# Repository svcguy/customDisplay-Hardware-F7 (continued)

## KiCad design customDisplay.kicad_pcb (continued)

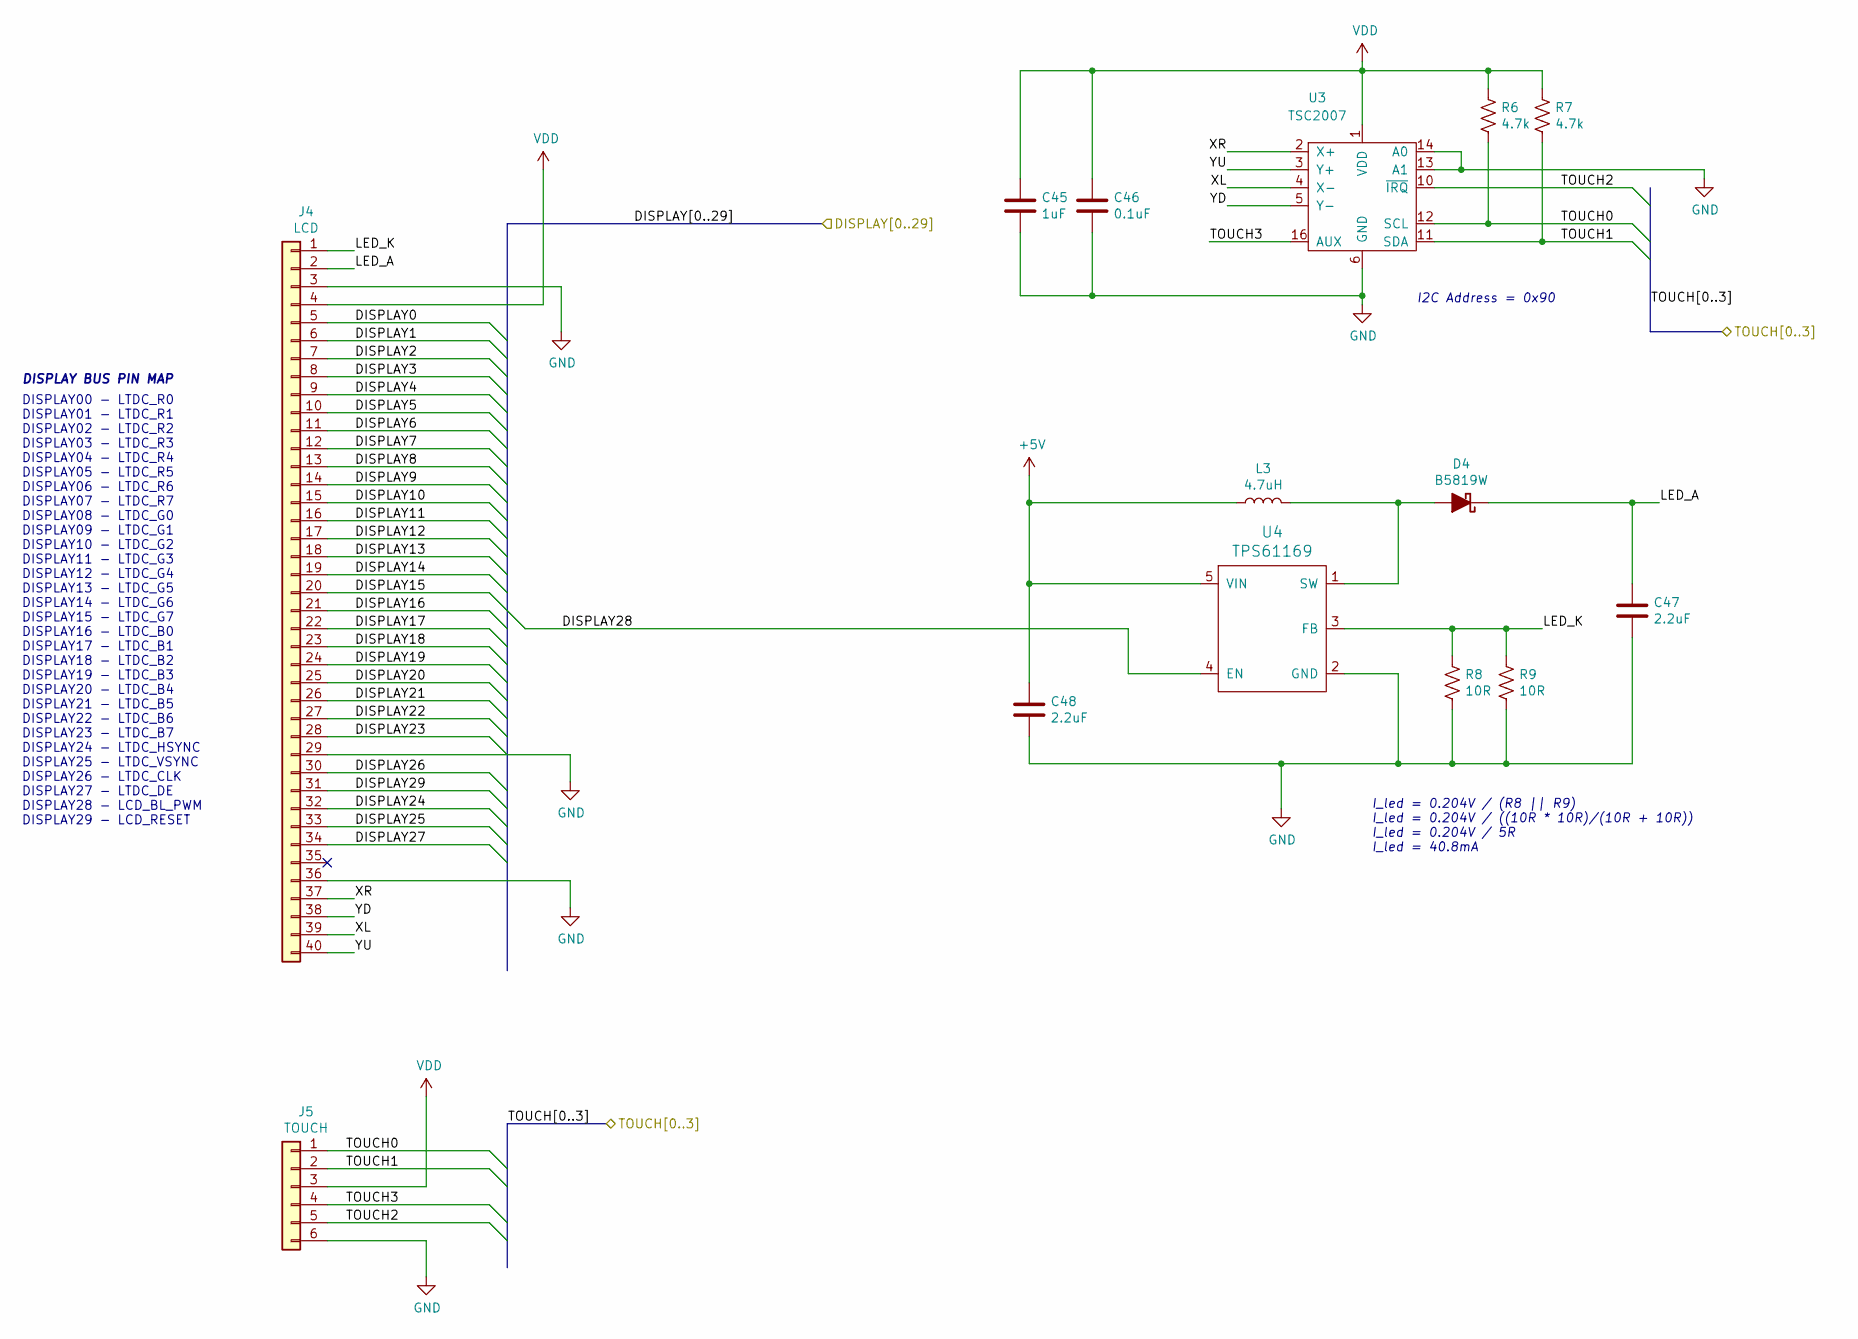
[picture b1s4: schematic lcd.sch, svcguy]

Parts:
C45: 1uF; C_0402_1005Metric; LCSC C52923
C46: 0.1uF; C_0402_1005Metric; LCSC C1525
C47, C48: 2.2uF; C_0603_1608Metric; LCSC C23630
D4: B5819W; D_SOD-123; LCSC C8598
J4: LCD; FH12A-40S-0.5SH_REVERSE_PIN_NUMBERING; LCSC C262686
J5: TOUCH; Hirose_FH12-6S-0.5SH_1x06-1MP_P0.50mm_Horizontal; LCSC C262287
L3: 4.7uH; MWSA0402; LCSC C408337
R6, R7: 4.7k; R_0402_1005Metric; LCSC C25900
R8, R9: 10R; R_1206_3216Metric; LCSC C17903
U3: TSC2007; HTSSOP-16-1EP_4.4x5mm_P0.65mm_EP3x3mm; LCSC C38398
U4: TPS61169; SC70; LCSC C71045

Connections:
+5V: C48.1, L3.1, U4.5 (VIN); also elsewhere on the board
/LCD/DISPLAY0: J4.5; also elsewhere on the board
/LCD/DISPLAY1: J4.6; also elsewhere on the board
/LCD/DISPLAY2: J4.7; also elsewhere on the board
/LCD/DISPLAY3: J4.8; also elsewhere on the board
/LCD/DISPLAY4: J4.9; also elsewhere on the board
/LCD/DISPLAY5: J4.10; also elsewhere on the board
/LCD/DISPLAY6: J4.11; also elsewhere on the board
/LCD/DISPLAY7: J4.12; also elsewhere on the board
/LCD/DISPLAY8: J4.13; also elsewhere on the board
/LCD/DISPLAY9: J4.14; also elsewhere on the board
/LCD/DISPLAY10: J4.15; also elsewhere on the board
/LCD/DISPLAY11: J4.16; also elsewhere on the board
/LCD/DISPLAY12: J4.17; also elsewhere on the board
/LCD/DISPLAY13: J4.18; also elsewhere on the board
/LCD/DISPLAY14: J4.19; also elsewhere on the board
/LCD/DISPLAY15: J4.20; also elsewhere on the board
/LCD/DISPLAY16: J4.21; also elsewhere on the board
/LCD/DISPLAY17: J4.22; also elsewhere on the board
/LCD/DISPLAY18: J4.23; also elsewhere on the board
/LCD/DISPLAY19: J4.24; also elsewhere on the board
/LCD/DISPLAY20: J4.25; also elsewhere on the board
/LCD/DISPLAY21: J4.26; also elsewhere on the board
/LCD/DISPLAY22: J4.27; also elsewhere on the board
/LCD/DISPLAY23: J4.28; also elsewhere on the board
/LCD/DISPLAY24: J4.32; also elsewhere on the board
/LCD/DISPLAY25: J4.33; also elsewhere on the board
/LCD/DISPLAY26: J4.30; also elsewhere on the board
/LCD/DISPLAY27: J4.34; also elsewhere on the board
/LCD/DISPLAY28: U4.4 (EN); also elsewhere on the board
/LCD/DISPLAY29: J4.31; also elsewhere on the board
/LCD/LED_A: C47.1, D4.1 (K), J4.2
/LCD/LED_K: J4.1, R8.1, R9.1, U4.3 (FB)
/LCD/TOUCH2: J5.5, U3.10 (~IRQ); also elsewhere on the board
/LCD/TOUCH3: J5.4, U3.16 (AUX); also elsewhere on the board
/LCD/XL: J4.39, U3.4 (X-)
/LCD/XR: J4.37, U3.2 (X+)
/LCD/YD: J4.38, U3.5 (Y-)
/LCD/YU: J4.40, U3.3 (Y+)
/TOUCH0: J5.1, R6.2, U3.12 (SCL); also elsewhere on the board
/TOUCH1: J5.2, R7.2, U3.11 (SDA); also elsewhere on the board
GND: C45.2, C46.2, C47.2, C48.2, J4.3, J4.29, J4.36, J5.6, R8.2, R9.2, U3.6 (GND), U3.13 (A1), U3.14 (A0), U3.17, U4.2 (GND); also elsewhere on the board
unnamed: D4.2 (A), L3.2, U4.1 (SW)
VDD: C45.1, C46.1, J4.4, J5.3, R6.1, R7.1, U3.1 (VDD); also elsewhere on the board

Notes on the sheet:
DISPLAY BUS PIN MAP
DISPLAY00 - LTDC_R0 DISPLAY01 - LTDC_R1 DISPLAY02 - LTDC_R2 DISPLAY03 - LTDC_R3 DISPLAY04 - LTDC_R4 DISPLAY05 - LTDC_R5 DISPLAY06 - LTDC_R6 DISPLAY07 - LTDC_R7 DISPLAY08 - LTDC_G0 DISPLAY09 - LTDC_G1 DISPLAY10 - LTDC_G2 DISPLAY11 - LTDC_G3 DISPLAY12 - LTDC_G4 DISPLAY13 - LTDC_G5 DISPLAY14 - LTDC_G6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
I_led = 0.204V / (R8 || R9) I_led = 0.204V / ((10R * 10R)/(10R + 10R)) I_led = 0.204V / 5R I_led = 40.8mA
I2C Address = 0x90

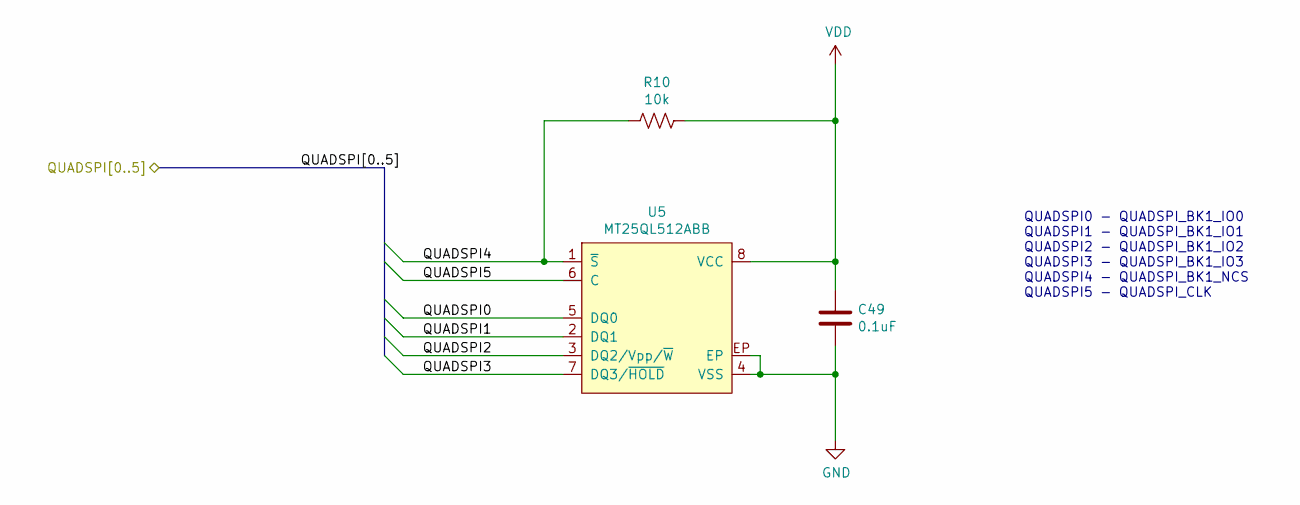
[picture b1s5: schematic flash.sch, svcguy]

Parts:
C49: 0.1uF; C_0402_1005Metric; LCSC C1525
R10: 10k; R_0402_1005Metric; LCSC C25744
U5: MT25QL512ABB; W-PDFN-8; LCSC C88868

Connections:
/Flash/QUADSPI0: U5.5 (DQ0); also elsewhere on the board
/Flash/QUADSPI1: U5.2 (DQ1); also elsewhere on the board
/Flash/QUADSPI2: U5.3 (DQ2/Vpp/~W); also elsewhere on the board
/Flash/QUADSPI3: U5.7 (DQ3/~HOLD); also elsewhere on the board
/Flash/QUADSPI4: R10.2, U5.1 (~S); also elsewhere on the board
/Flash/QUADSPI5: U5.6 (C); also elsewhere on the board
GND: C49.2, U5.4 (VSS), U5.12, U5.EP; also elsewhere on the board
VDD: C49.1, R10.1, U5.8 (VCC); also elsewhere on the board

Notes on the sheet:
QUADSPI0 - QUADSPI_BK1_IO0 QUADSPI1 - QUADSPI_BK1_IO1 QUADSPI2 - QUADSPI_BK1_IO2 QUADSPI3 - QUADSPI_BK1_IO3 QUADSPI4 - QUADSPI_BK1_NCS QUADSPI5 - QUADSPI_CLK

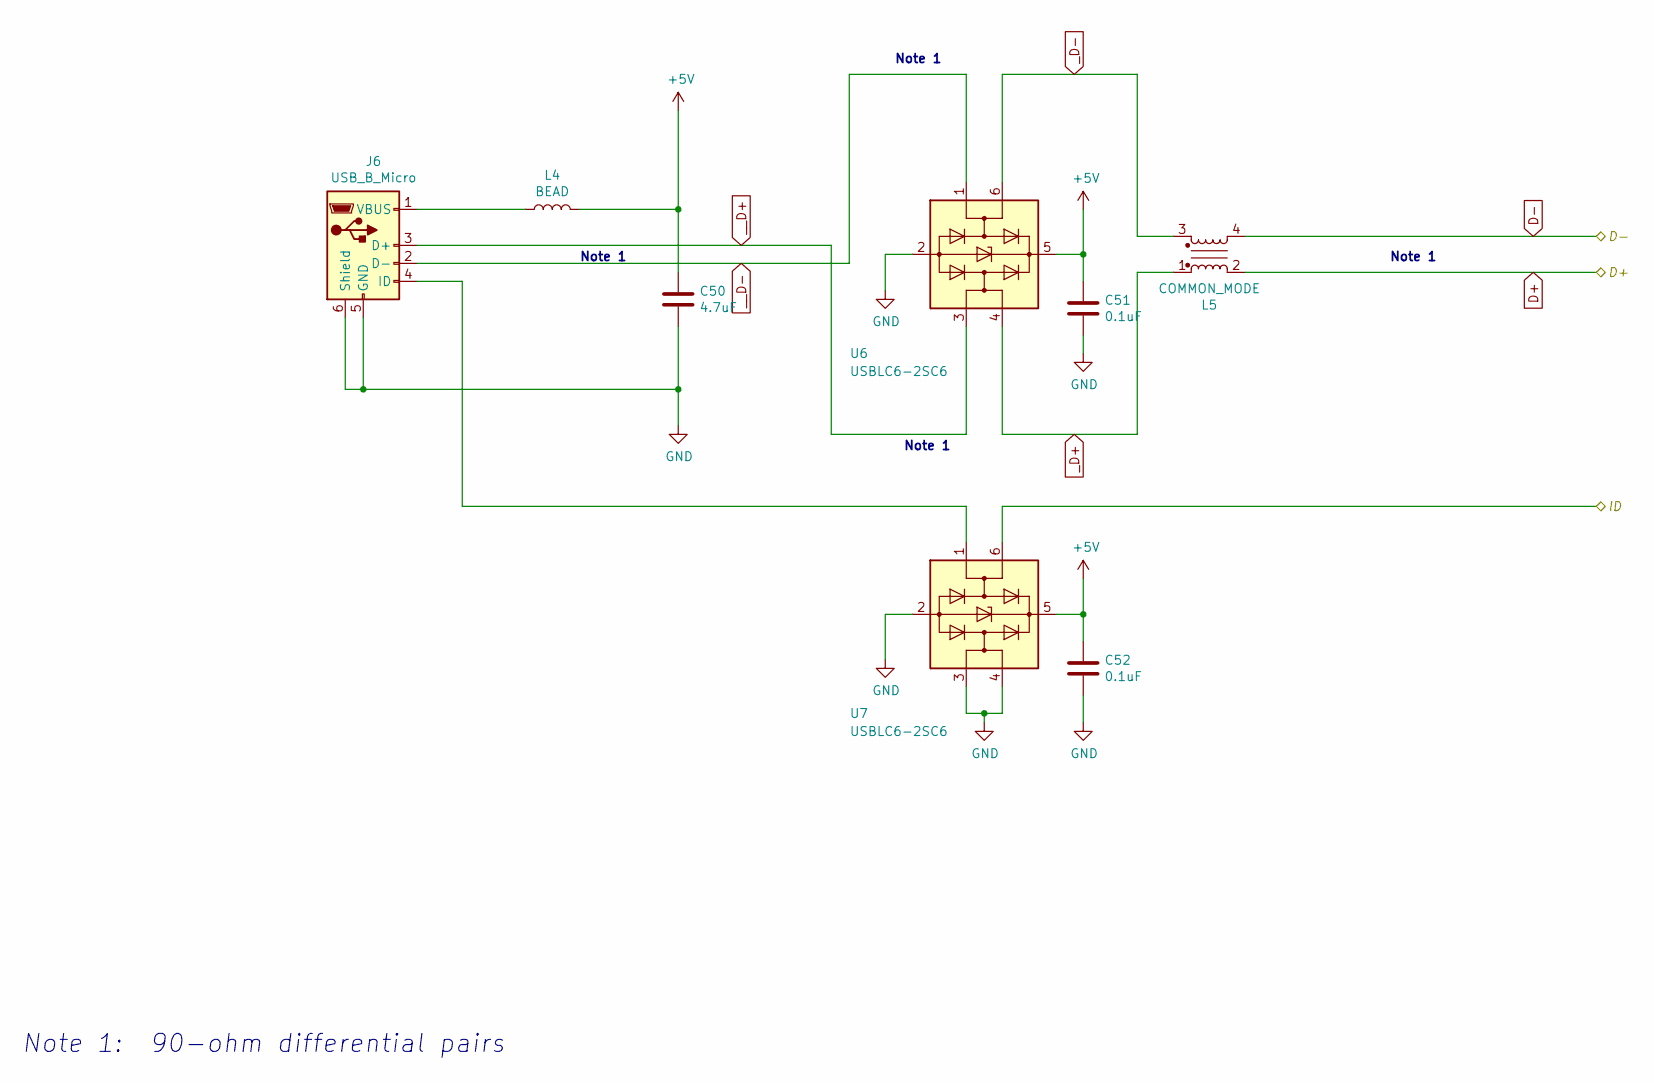
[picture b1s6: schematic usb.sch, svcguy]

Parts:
C50: 4.7uF; C_0805_2012Metric; LCSC C1779
C51, C52: 0.1uF; C_0402_1005Metric; LCSC C1525
J6: USB_B_Micro; USB_Micro-B_Amphenol_10103594-0001LF_Horizontal; LCSC C428495
L4: BEAD; L_0805_2012Metric; LCSC C1015
L5: COMMON_MODE; COMMON_MODE_FILTER_0805; LCSC C54888
U6, U7: USBLC6-2SC6; SOT-23-6; LCSC C7519

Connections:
+5V: C50.1, C51.1, C52.1, L4.2, U6.5 (VBUS), U7.5 (VBUS); also elsewhere on the board
/USB/ID: U7.6 (I/O1); also elsewhere on the board
D+: L5.2; also elsewhere on the board
D-: L5.4; also elsewhere on the board
GND: C50.2, C51.2, C52.2, J6.5 (GND), J6.6 (Shield), U6.2 (GND), U7.2 (GND), U7.3 (I/O2), U7.4 (I/O2); also elsewhere on the board
unnamed: J6.1 (VBUS), L4.1
unnamed: J6.4 (ID), U7.1 (I/O1)
_D+: L5.1, U6.4 (I/O2)
_D-: L5.3, U6.6 (I/O1)
__D+: J6.3 (D+), U6.3 (I/O2)
__D-: J6.2 (D-), U6.1 (I/O1)

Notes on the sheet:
Note 1
Note 1: 90-ohm differential pairs

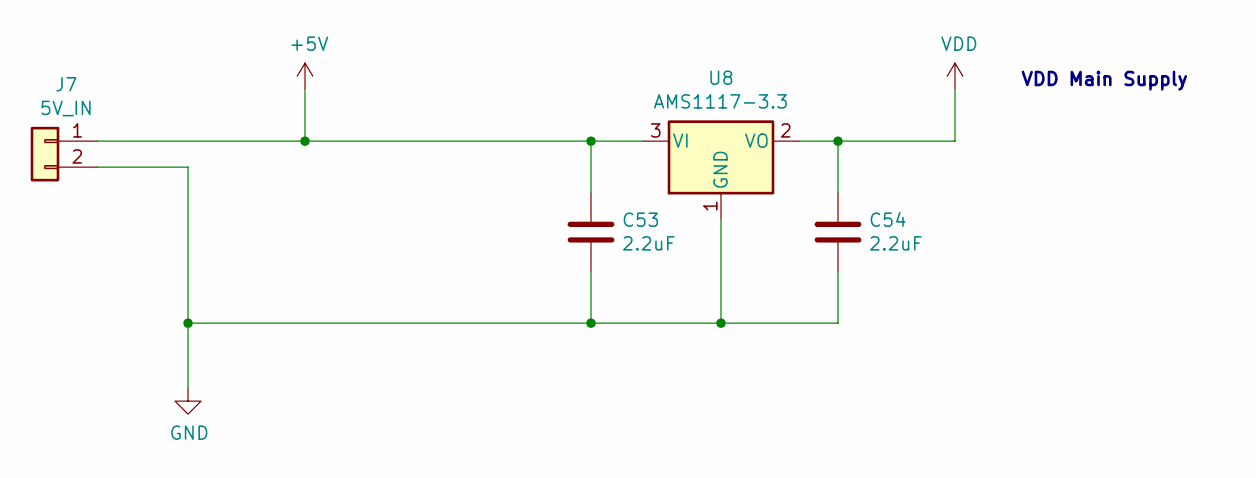
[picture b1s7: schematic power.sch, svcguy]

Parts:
C53, C54: 2.2uF; C_0603_1608Metric; LCSC C23630
J7: 5V_IN; PinHeader_1x02_P2.54mm_Vertical; LCSC DNP
U8: AMS1117-3.3; SOT-223-3_TabPin2; LCSC C6186

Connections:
+5V: C53.1, J7.1, U8.3 (VI); also elsewhere on the board
GND: C53.2, C54.2, J7.2, U8.1 (GND); also elsewhere on the board
VDD: C54.1, U8.2 (VO); also elsewhere on the board

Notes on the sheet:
VDD Main Supply

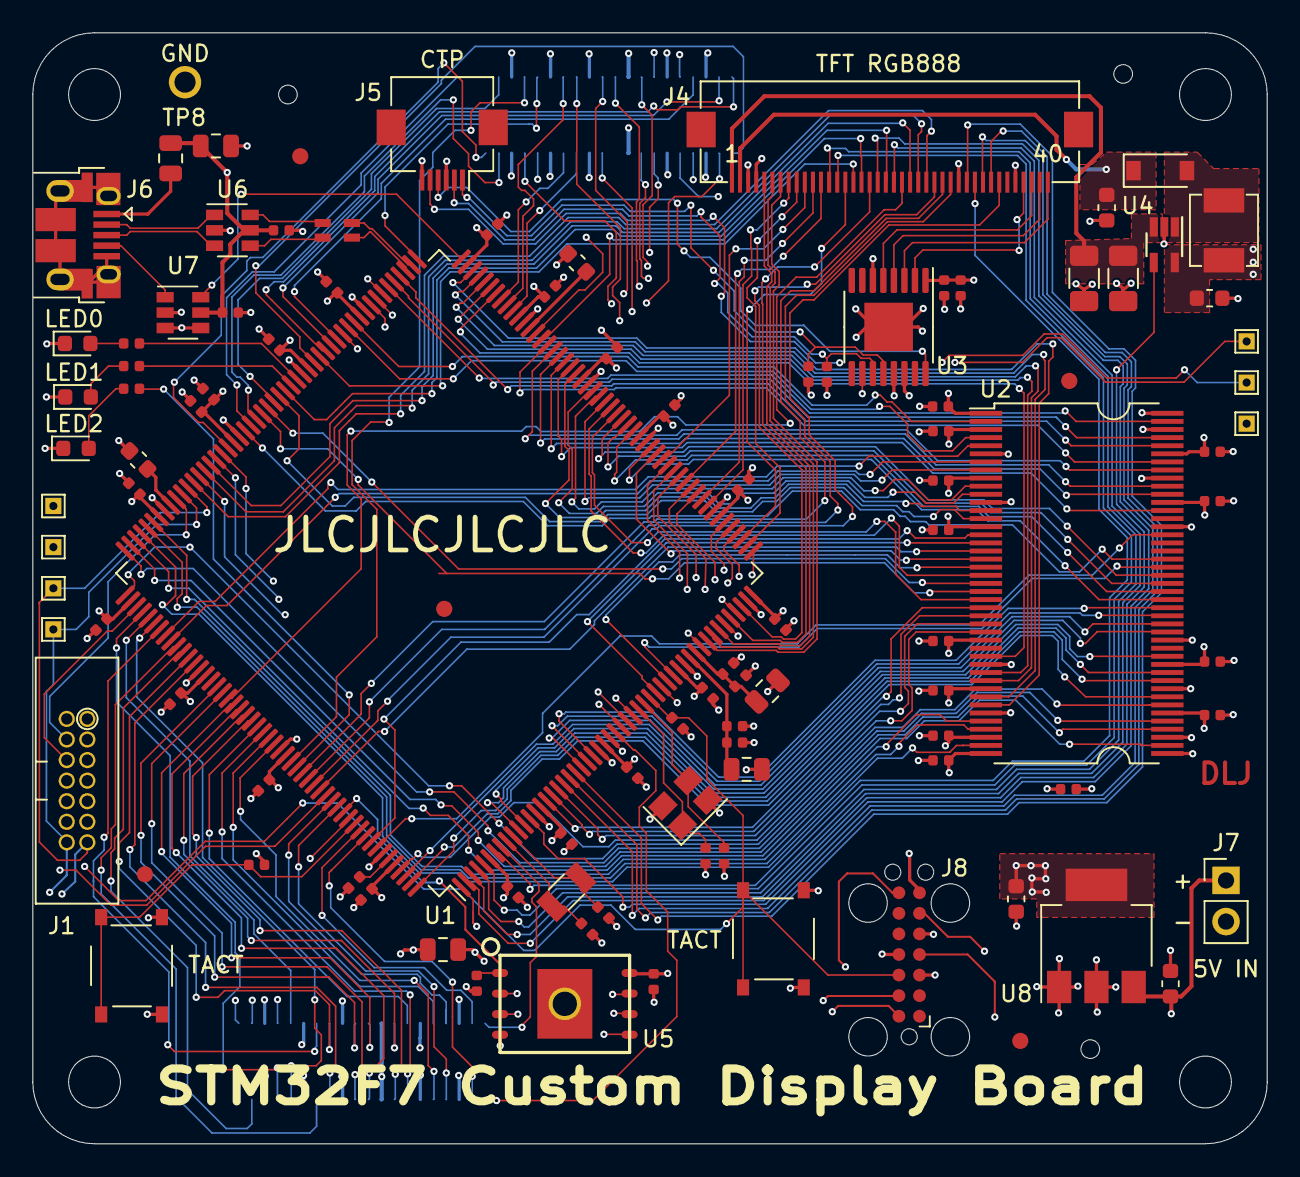
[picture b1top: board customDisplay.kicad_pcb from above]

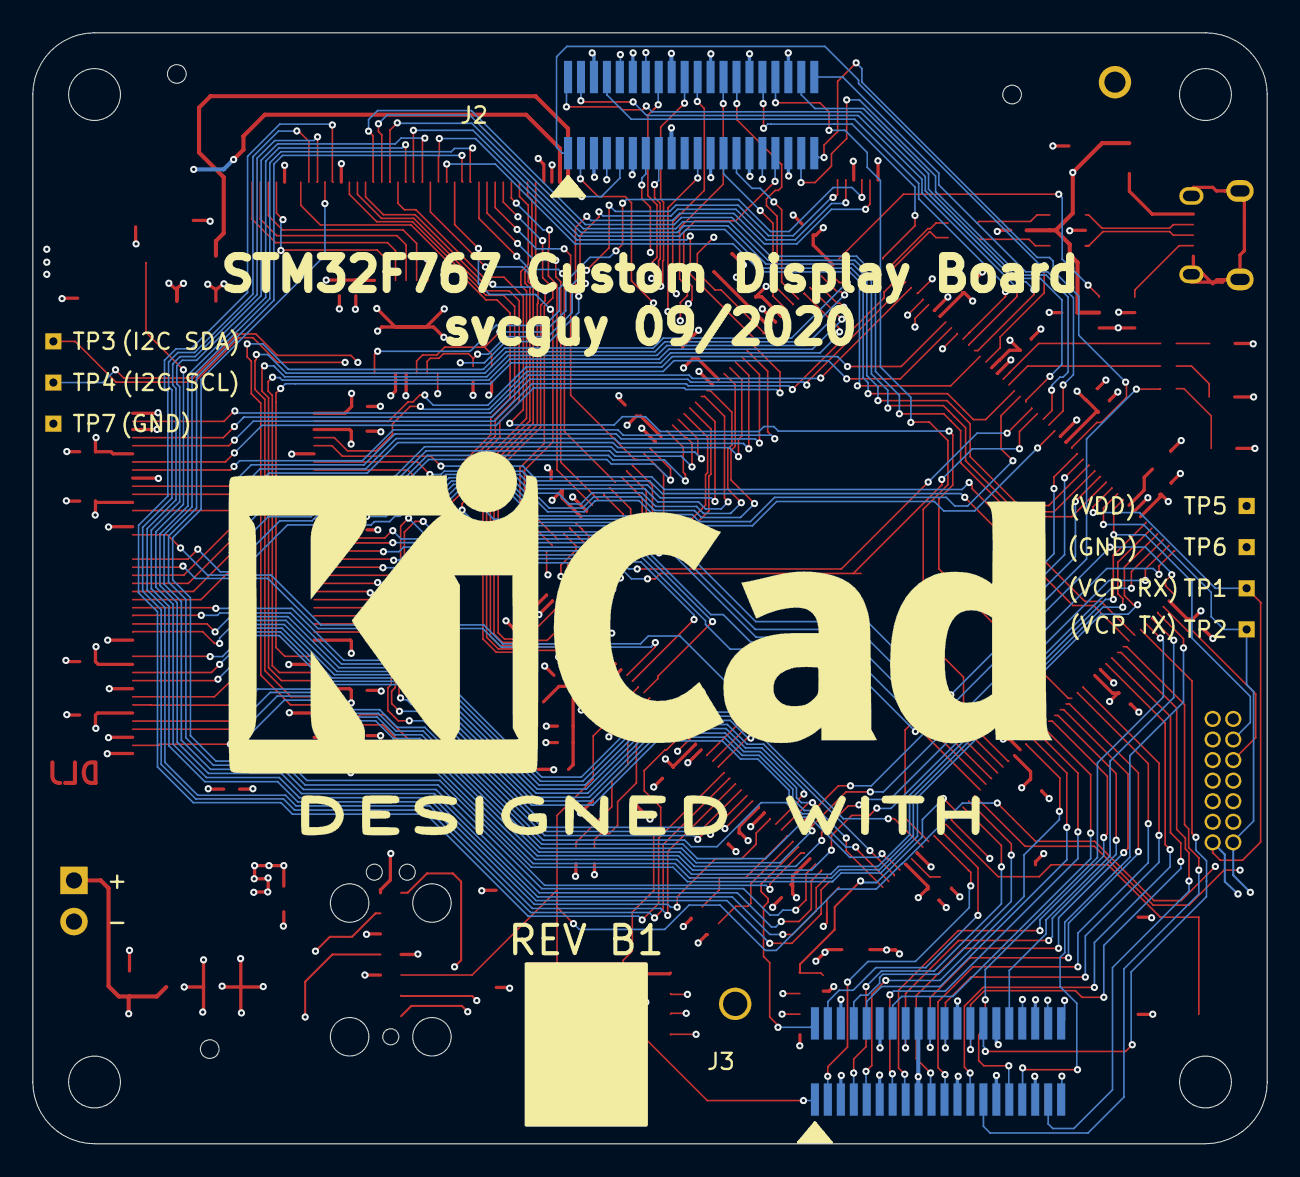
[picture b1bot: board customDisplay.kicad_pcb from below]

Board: 4 copper layers, 76.2 x 68.6 mm, 113 parts (2 on the bottom side), 193 nets.

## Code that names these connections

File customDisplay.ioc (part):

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Mcu.Name=STM32F767B(G-I)Tx
Mcu.Package=LQFP208
Mcu.UserName=STM32F767BGTx
PA1.Mode=RGB888
PA1.Signal=LTDC_R2
PA10.Mode=RGB888
PA10.Signal=LTDC_B4
PA11.GPIOParameters=GPIO_Label
PA11.GPIO_Label=VCP_RX
PA11.Mode=Asynchronous
PA11.Signal=UART4_RX
PA12.GPIOParameters=GPIO_Label
PA12.GPIO_Label=VCP_TX
PA12.Mode=Asynchronous
PA12.Signal=UART4_TX
PA13.Mode=Trace_Asynchronous_SW
PA13.Signal=SYS_JTMS-SWDIO
PA14.Mode=Trace_Asynchronous_SW
PA14.Signal=SYS_JTCK-SWCLK
PA2.Mode=RGB888
PA2.Signal=LTDC_R1
PA3.Mode=RGB888
PA3.Signal=LTDC_B5
PA5.Mode=RGB888
PA5.Signal=LTDC_R4
PA6.Mode=RGB888
PA6.Signal=LTDC_G2
PA8.Mode=RGB888
PA8.Signal=LTDC_B3
PB0.Mode=RGB888
PB0.Signal=LTDC_R3
PB1.Mode=RGB888
PB1.Signal=LTDC_R6
PB10.Mode=RGB888
PB10.Signal=LTDC_G4
PB12.Mode=OTG/Dual-Role-Device-FS
PB12.Signal=USB_OTG_HS_ID
PB14.Mode=OTG/Dual-Role-Device-FS
PB14.Signal=USB_OTG_HS_DM
PB15.Mode=OTG/Dual-Role-Device-FS
PB15.Signal=USB_OTG_HS_DP
PB3.Mode=Trace_Asynchronous_SW
PB3.Signal=SYS_JTDO-SWO
PB6.Mode=Single Bank 1
PB6.Signal=QUADSPI_BK1_NCS
PC0.Signal=FMC_SDNWE
PC14/OSC32_IN.Mode=LSE-External-Oscillator
PC14/OSC32_IN.Signal=RCC_OSC32_IN
PC15/OSC32_OUT.Mode=LSE-External-Oscillator
PC15/OSC32_OUT.Signal=RCC_OSC32_OUT
PC2.Mode=SdramChipSelect1_1
PC2.Signal=FMC_SDNE0
PC3.Mode=SdramChipSelect1_1
PC3.Signal=FMC_SDCKE0
PC9.Mode=RGB888
PC9.Signal=LTDC_B2
PD0.Signal=FMC_D2_DA2
PD1.Signal=FMC_D3_DA3
PD10.Signal=FMC_D15_DA15
PD11.GPIOParameters=GPIO_Label
PD11.GPIO_Label=TOUCH_INT
PD11.Signal=GPXTI11
PD12.Mode=I2C
PD12.Signal=I2C4_SCL
PD13.Mode=I2C
PD13.Signal=I2C4_SDA
PD14.Signal=FMC_D0_DA0
PD15.Signal=FMC_D1_DA1
PD8.Signal=FMC_D13_DA13
PD9.Signal=FMC_D14_DA14
PE0.Signal=FMC_NBL0
PE1.Signal=FMC_NBL1
PE10.Signal=FMC_D7_DA7
PE11.Signal=FMC_D8_DA8
PE12.Signal=FMC_D9_DA9
PE13.Signal=FMC_D10_DA10
PE14.Signal=FMC_D11_DA11
PE15.Signal=FMC_D12_DA12
PE2.Mode=Single Bank 1
PE2.Signal=QUADSPI_BK1_IO2
PE4.Mode=RGB888
PE4.Signal=LTDC_B0
PE5.Mode=RGB888
PE5.Signal=LTDC_G0
PE6.Mode=RGB888
PE6.Signal=LTDC_G1
PE7.Signal=FMC_D4_DA4
PE8.Signal=FMC_D5_DA5
PE9.Signal=FMC_D6_DA6
PF0.Signal=FMC_A0
PF1.Signal=FMC_A1
PF10.Mode=Single Bank 1
PF10.Signal=QUADSPI_CLK
PF11.Signal=FMC_SDNRAS
PF12.Signal=FMC_A6
PF13.Signal=FMC_A7
PF14.Signal=FMC_A8
PF15.Signal=FMC_A9
PF2.Signal=FMC_A2
PF3.Signal=FMC_A3
PF4.Signal=FMC_A4
PF5.Signal=FMC_A5
PF6.Mode=Single Bank 1
PF6.Signal=QUADSPI_BK1_IO3
PF8.Mode=Single Bank 1
PF8.Signal=QUADSPI_BK1_IO0
PF9.Mode=Single Bank 1
PF9.Signal=QUADSPI_BK1_IO1
PG0.Signal=FMC_A10
PG1.Signal=FMC_A11
PG15.Signal=FMC_SDNCAS
PG4.Signal=FMC_A14_BA0
PG5.Signal=FMC_A15_BA1
PG8.Signal=FMC_SDCLK
PH0/OSC_IN.Mode=HSE-External-Oscillator
PH0/OSC_IN.Signal=RCC_OSC_IN
PH1/OSC_OUT.Mode=HSE-External-Oscillator
PH1/OSC_OUT.Signal=RCC_OSC_OUT
PH10.Signal=FMC_D18
PH11.Signal=FMC_D19
PH12.Signal=FMC_D20
PH13.Signal=FMC_D21
PH14.Signal=FMC_D22
PH15.Signal=FMC_D23
PH2.Mode=RGB888
PH2.Signal=LTDC_R0
PH4.Mode=RGB888
PH4.Signal=LTDC_G5
PH8.Signal=FMC_D16
PH9.Signal=FMC_D17
PI0.Signal=FMC_D24
PI1.Signal=FMC_D25
PI10.Signal=FMC_D31
PI11.Mode=RGB888
PI11.Signal=LTDC_G6
PI12.Mode=RGB888
PI12.Signal=LTDC_HSYNC
PI13.Mode=RGB888
PI13.Signal=LTDC_VSYNC
PI14.Mode=RGB888
PI14.Signal=LTDC_CLK
PI2.Signal=FMC_D26
PI3.Signal=FMC_D27
PI4.Signal=FMC_NBL2
PI5.Signal=FMC_NBL3
PI6.Signal=FMC_D28
PI7.Signal=FMC_D29
PI9.Signal=FMC_D30
PJ0.Mode=RGB888
PJ0.Signal=LTDC_R7
PJ10.Mode=RGB888
PJ10.Signal=LTDC_G3
PJ13.Mode=RGB888
PJ13.Signal=LTDC_B1
PJ4.Mode=RGB888
PJ4.Signal=LTDC_R5
PK0.GPIOParameters=GPIO_Label
PK0.GPIO_Label=LED0
PK0.Signal=GPIO_Output
PK1.GPIOParameters=GPIO_Label
PK1.GPIO_Label=LED1
PK1.Signal=GPIO_Output
PK2.Mode=RGB888
PK2.Signal=LTDC_G7
PK5.Mode=RGB888
PK5.Signal=LTDC_B6
PK6.Mode=RGB888
PK6.Signal=LTDC_B7
PK7.Mode=RGB888
PK7.Signal=LTDC_DE
RCC.HSE_VALUE=25000000
RCC.SYSCLKFreq_VALUE=216000000
RCC.SYSCLKSource=RCC_SYSCLKSOURCE_PLLCLK
board=custom

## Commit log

2020-09-26 Update to REV B1
